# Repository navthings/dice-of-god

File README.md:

dice of god

hey didnt einstein say god didnt play dice with the universe?

fuck einstein im cooler then you im gonna make a physics breaker to prove you wrong ahahhaha

what it is

a dice that rolls using radioactive decay. a geiger tube clicks every time a particle flies through it and nobody can predict when that happens, so the pico uses the timing of each click to pick a number from 1 to 6. building for hack club fallen

how it works

usb 5v goes into a 555 timer and a coil that pump it up to 400v for the tube (four zeners stop it at 400). every click goes through a transistor into the pico, the pico looks at its clock at that exact moment and lights up the dice leds

whats in here

pcb is in pcb/ (kicad), gerbers are pcb/dice-of-god-gerbers.zip, just upload to jlc
parts are in bom.csv
hv-supply.txt is the falstad sim of the 400v supply
code comes when the parts do

pcb

schematic

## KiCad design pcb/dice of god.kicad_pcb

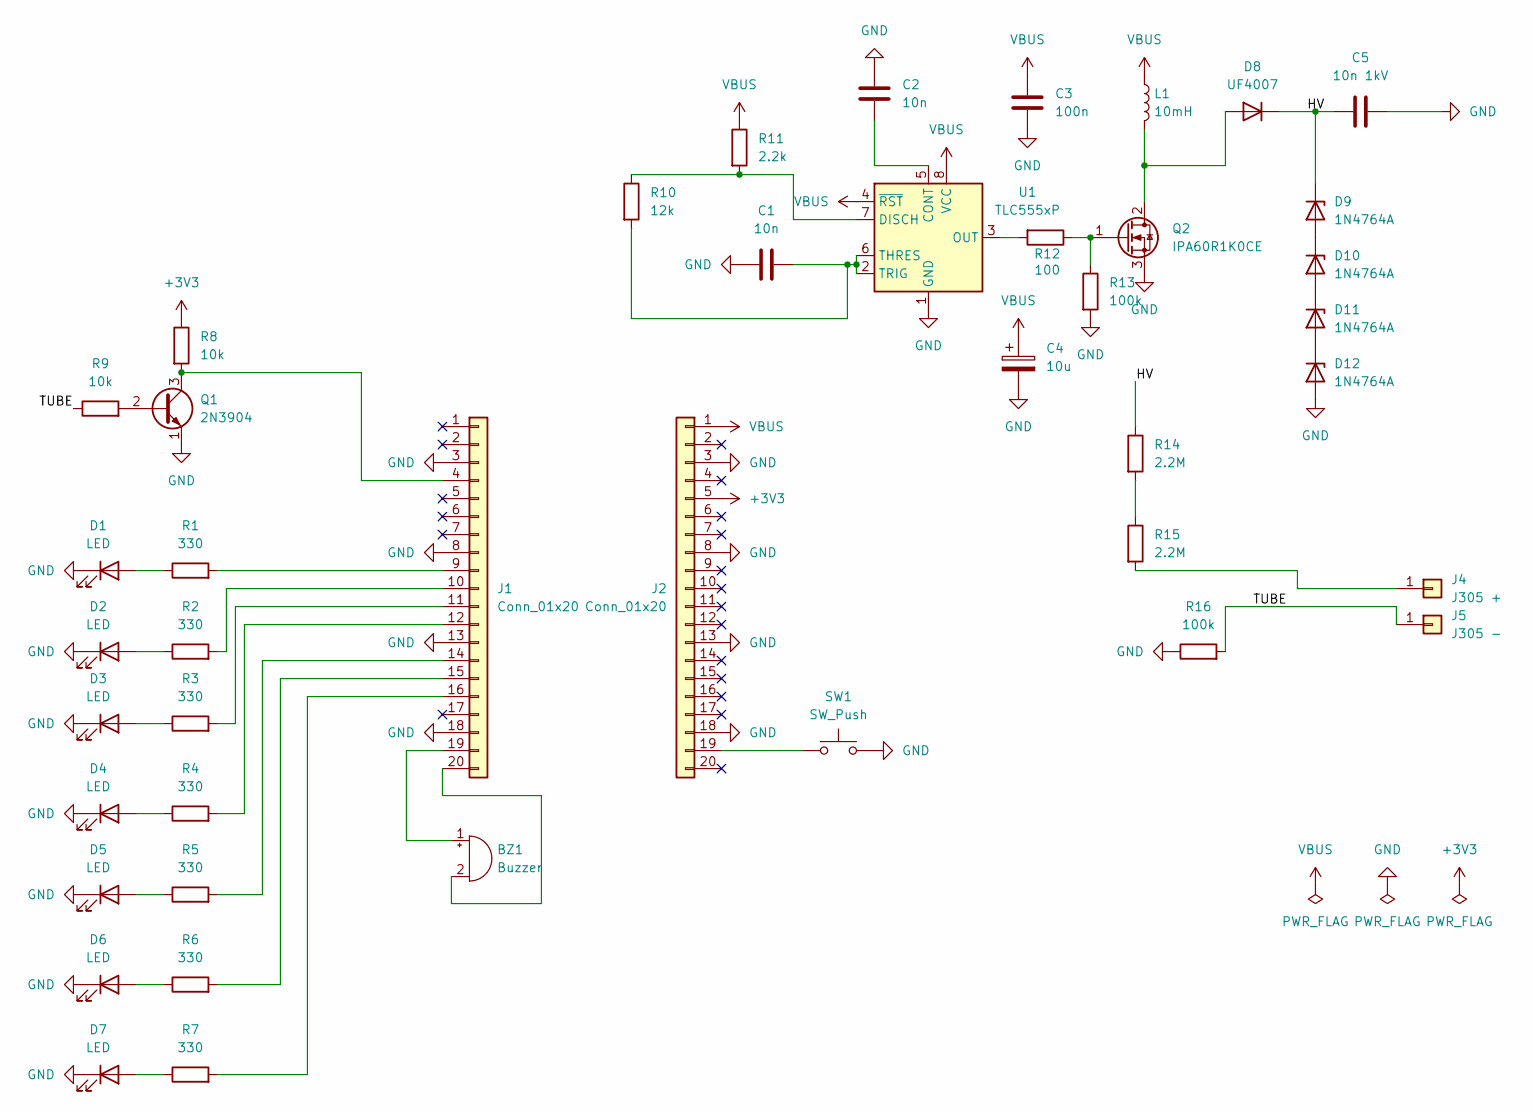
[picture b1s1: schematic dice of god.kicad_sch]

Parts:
BZ1: Buzzer; Buzzer_TDK_PS1240P02BT_D12.2mm_H6.5mm
C1, C2: 10n; C_Disc_D5.0mm_W2.5mm_P5.00mm
C3: 100n; C_Disc_D5.0mm_W2.5mm_P5.00mm
C4: 10u; CP_Radial_D5.0mm_P2.00mm
C5: 10n 1kV; C_Disc_D10.5mm_W5.0mm_P7.50mm
D1, D2, D3, D4, D5, D6, D7: LED; LED_D5.0mm
D8: UF4007; D_DO-41_SOD81_P10.16mm_Horizontal
D9, D10, D11, D12: 1N4764A; D_DO-41_SOD81_P10.16mm_Horizontal
J1, J2: Conn_01x20; PinSocket_1x20_P2.54mm_Vertical
J4: J305 +; TestPoint_THTPad_D3.0mm_Drill1.5mm
J5: J305 −; TestPoint_THTPad_D3.0mm_Drill1.5mm
L1: 10mH; L_Radial_D12.5mm_P7.00mm_Fastron_09HCP
Q1: 2N3904; TO-92_Inline_Wide
Q2: IPA60R1K0CE; TO-220-3_Vertical
R1, R2, R3, R4, R5, R6, R7: 330; R_Axial_DIN0207_L6.3mm_D2.5mm_P10.16mm_Horizontal
R8, R9: 10k; R_Axial_DIN0207_L6.3mm_D2.5mm_P10.16mm_Horizontal
R10: 12k; R_Axial_DIN0207_L6.3mm_D2.5mm_P10.16mm_Horizontal
R11: 2.2k; R_Axial_DIN0207_L6.3mm_D2.5mm_P10.16mm_Horizontal
R12: 100; R_Axial_DIN0207_L6.3mm_D2.5mm_P10.16mm_Horizontal
R13, R16: 100k; R_Axial_DIN0207_L6.3mm_D2.5mm_P10.16mm_Horizontal
R14, R15: 2.2M; R_Axial_DIN0207_L6.3mm_D2.5mm_P15.24mm_Horizontal
SW1: SW_Push; SW_PUSH_6mm
U1: TLC555xP; DIP-8_W7.62mm

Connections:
+3V3: J2.5, R8.1
/HV: C5.1, D8.1 (K), D9.1 (K), R14.1
/TUBE: J5.1 (Pin_1_1), R9.1, R16.2
GND: C1.1, C2.1, C3.2, C4.2, C5.2, D1.1 (K), D2.1 (K), D3.1 (K), D4.1 (K), D5.1 (K), D6.1 (K), D7.1 (K), D12.2 (A), J1.3, J1.8, J1.13, J1.18, J2.3, J2.8, J2.13, J2.18, Q1.1 (E), Q2.3 (S), R13.2, R16.1, SW1.2, U1.1 (GND)
unnamed: BZ1.1 (+), J1.19
unnamed: BZ1.2 (-), J1.20
unnamed: D1.2 (A), R1.1
unnamed: D2.2 (A), R2.1
unnamed: D3.2 (A), R3.1
unnamed: D4.2 (A), R4.1
unnamed: D5.2 (A), R5.1
unnamed: D6.2 (A), R6.1
unnamed: D7.2 (A), R7.1
unnamed: D8.2 (A), L1.2, Q2.2 (D)
unnamed: D10.2 (A), D11.1 (K)
unnamed: D9.2 (A), D10.1 (K)
unnamed: D11.2 (A), D12.1 (K)
unnamed: J1.4, Q1.3 (C), R8.2
unnamed: J1.9, R1.2
unnamed: J1.10, R2.2
unnamed: J1.11, R3.2
unnamed: J1.12, R4.2
unnamed: J1.14, R5.2
unnamed: J1.15, R6.2
unnamed: J1.16, R7.2
unnamed: J2.19, SW1.1
unnamed: J4.1 (Pin_1_1), R15.2
unnamed: Q1.2 (B), R9.2
unnamed: Q2.1 (G), R12.1, R13.1
unnamed: R14.2, R15.1
unnamed: C2.2, U1.5 (CONT)
unnamed: R10.1, R11.2, U1.7 (DISCH)
unnamed: R12.2, U1.3 (OUT)
unnamed: C1.2, R10.2, U1.2 (TRIG), U1.6 (THRES)
VBUS: C3.1, C4.1, J2.1, L1.1, R11.1, U1.4 (~RST), U1.8 (VCC)

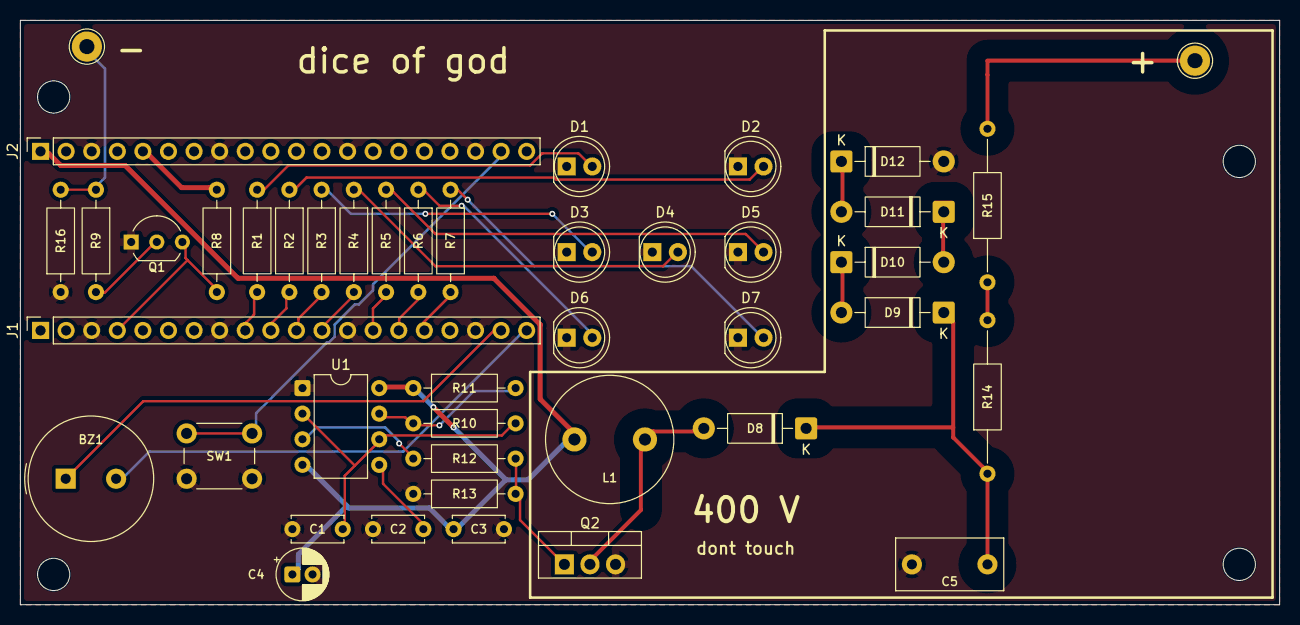
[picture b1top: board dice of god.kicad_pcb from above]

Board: 2 copper layers, 125.0 x 58.0 mm, 47 parts (0 on the bottom side), 35 nets.

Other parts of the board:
H1, H2, H3, H4: MountingHole_3.2mm_M3

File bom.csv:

"Item","Qty","Supplier","SKU","Unit (USD)","Total (USD)","Link","Why"
"Raspberry Pi Pico 2H (with headers)","1","Core Electronics","CE10154","6.93","6.93","https://core-electronics.com.au/catalog/product/view/sku/CE10154","the brain, plugs into the two sockets (J1/J2). AU$9.90"
"J305 geiger tube, glass, 107mm","2","AliExpress","J305 107mm","19.78","39.56","https://www.aliexpress.com/w/wholesale-j305-gm.html","the detector, clicks when a particle goes through it; 1 spare since its glass and ships from china. pick the 107mm option"
"TLC555CP timer (DIP-8)","1","DigiKey","TLC555CP","1.48","1.48","https://www.digikey.com/en/products/result?keywords=TLC555CP","U1, the clock that drives the 400V pump"
"DIP-8 socket","1","DigiKey","ED08DT","0.47","0.47","https://www.digikey.com/en/products/result?keywords=ED08DT","so the 555 isnt soldered in directly"
"600V MOSFET, TO-220 FullPAK","2","DigiKey","IPA60R1K0CEXKSA1","1.49","2.98","https://www.digikey.com/en/products/result?keywords=IPA60R1K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","Q2, the pump switch. plastic tab so nothing live to touch, turns on from 5V (Vth max 3.5V); 1 spare"
"10mH radial inductor, 100mA, 12 ohm","1","DigiKey","RLB1314-103KL","0.57","0.57","https://www.digikey.com/en/products/result?keywords=RLB1314-103KL","L1, stores energy and kicks it out at high voltage"
"UF4007 fast diode","2","DigiKey","UF4007-E3/54","0.85","1.70","https://www.digikey.com/en/products/result?keywords=UF4007-E3/54","D8, one way valve into the 400V cap; 1 spare"
"1N4764A 100V zener","5","DigiKey","1N4764A (Good-Ark)","0.29","1.45","https://www.digikey.com/en/products/result?keywords=1N4764A","D9-D12, four in a row cap the voltage at 400V; 1 spare"
"10nF 1kV ceramic disc, 7.5mm pitch","1","DigiKey","S103M47Z5UN63K7R","0.47","0.47","https://www.digikey.com/en/products/result?keywords=S103M47Z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","C5, holds the 400V"
"2N3904 transistor","1","DigiKey","2N3904BU","0.29","0.29","https://www.digikey.com/en/products/result?keywords=2N3904BU","Q1, turns each tube click into a pulse the pico can read"
"10nF 50V ceramic, 5mm pitch","2","DigiKey","K103K15X7RF53H5","0.26","0.52","https://www.digikey.com/en/products/result?keywords=K103K15X7RF53H5","C1 (555 timing) and C2 (555 pin 5)"
"100nF 50V ceramic, 5mm pitch","1","DigiKey","K104K15X7RF53H5","0.27","0.27","https://www.digikey.com/en/products/result?keywords=K104K15X7RF53H5","C3, smooths the 5V next to the 555"
"10uF 63V electrolytic, 5mm can","1","DigiKey","ECA-1JM100","0.26","0.26","https://www.digikey.com/en/products/result?keywords=ECA-1JM100","C4, stops the pump dragging the pico's 5V around (25V version is backordered, 63V is the same size)"
"330 ohm resistor 1/4W","7","DigiKey","MFR-25FBF52-330R","0.11","0.77","https://www.digikey.com/en/products/result?keywords=MFR-25FB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","R1-R7, one per dice LED (about 4mA each)"
"10k resistor 1/4W","2","DigiKey","MFR-25FBF52-10K","0.10","0.20","https://www.digikey.com/en/products/result?keywords=MFR-25FBF52-10K","R8 pull-up and R9 base resistor for Q1"
"12k resistor 1/4W","1","DigiKey","MFR-25FBF52-12K","0.10","0.10","https://www.digikey.com/en/products/result?keywords=MFR-25FBF52-12K","R10, 555 timing"
"2.2k resistor 1/4W","1","DigiKey","MFR-25FBF52-2K2","0.10","0.10","https://www.digikey.com/en/products/result?keywords=MFR-25FBF52-2K2","R11, 555 timing"
"100 ohm resistor 1/4W","1","DigiKey","MFR-25FBF52-100R","0.10","0.10","https://www.digikey.com/en/products/result?keywords=MFR-25FB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","R12, gate resistor for Q2"
"100k resistor 1/4W","2","DigiKey","CFR-25JB-52-100K","0.11","0.22","https://www.digikey.com/en/products/result?keywords=CFR-25JB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","R13 keeps Q2 off at power up, R16 turns the click current into a voltage"
"2.2M resistor 1/4W","2","DigiKey","CFR-25JB-52-2M2","0.10","0.20","https://www.digikey.com/en/products/result?keywords=CFR-25JB-52-2M2","R14 + R15, limit the tube current (two in series so each only sees 200V)"
"5mm red LED","7","DigiKey","WP7113ID","0.21","1.47","https://www.digikey.com/en/products/result?keywords=WP7113ID","D1-D7, the dice face"
"1x20 female header, 2.54mm","2","DigiKey","PPTC201LFBN-RC","1.14","2.28","https://www.digikey.com/en/products/result?keywords=PPTC201LFBN-RC","J1/J2, the pico sits on these so the resistors fit underneath it"
"6mm tactile button","1","DigiKey","1825910-6","0.12","0.12","https://www.digikey.com/en/products/result?keywords=1825910-6","SW1, roll button"
"Piezo buzzer TDK PS1240","1","DigiKey","PS1240P02BT","0.73","0.73","https://www.digikey.com/en/products/result?keywords=PS1240P02BT","BZ1, the geiger click sound"
"M3 x 10mm nylon standoffs (10 sets)","1","Core Electronics","FIT0066","1.66","1.66","https://core-electronics.com.au/10-sets-m3-10-nylon-standoff.html","lifts the board so the 400V solder joints on the back never touch the desk. nylon so nothing metal near the HV corner. AU$2.37"
"PCB, 100x58mm 2 layer, 5pcs","1","JLCPCB","dice-of-god-gerbers.zip","2.00","2.00","https://jlcpcb.com","the board (FR-4, 1.6mm, LeadFree HASL), under 100x100 so its the $2 tier. shipping extra"
"TOTAL","","","","","66.90","","parts + pcb, before shipping. checked 15 nov 2026, AUD at 0.70"
